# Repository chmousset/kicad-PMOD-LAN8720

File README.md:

# PMOD-LAN8720

This is a single-width PMOD module with the RMII 10/100BASE-T PHY LAN8720. Contrary to most similar Ethernet PHY extensions, this one requires the refclk signal has to be provided from the host. It can be useful when multiple PHY have to be connected as it can reduce usage of clock-domain crossing.

## Configuration
The configuration straps are set for RMII slave operation, and link autonegociation. The MDIO is broken down on an extra connector for diagnostic or testing purposes. PHY ID 0 is used.

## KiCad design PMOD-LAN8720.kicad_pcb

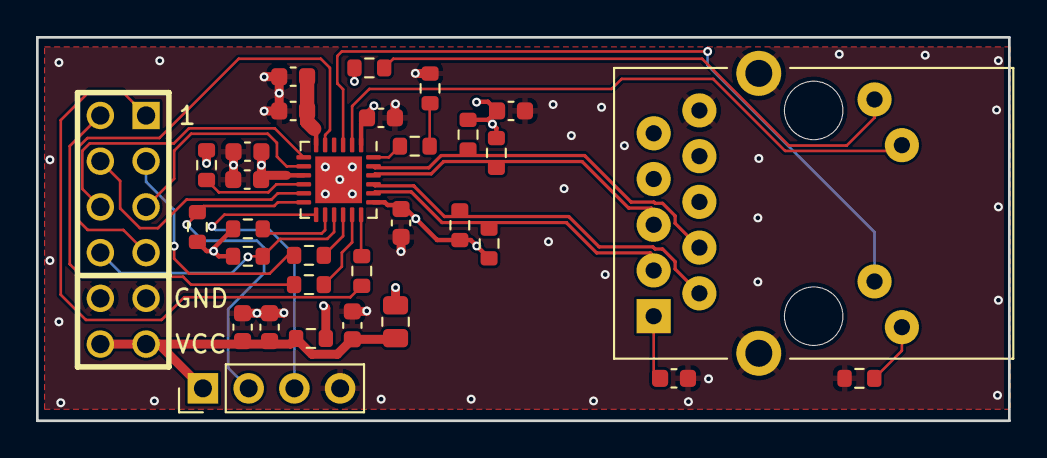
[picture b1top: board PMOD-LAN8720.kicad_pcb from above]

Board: 4 copper layers, 54.0 x 21.3 mm, 32 parts (0 on the bottom side), 31 nets.

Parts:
C10, C17, C22: 4.7u; C_0603_1608Metric
C12, C14, C23, C24, C27: 100n; C_0603_1608Metric
C15: 10p; C_0603_1608Metric
C19: 470p; C_0603_1608Metric
C21: 20p; C_0603_1608Metric
FB2: 100@100M; R_0805_2012Metric
J1: Conn_01x03; PinHeader_1x04_P2.54mm_Vertical
J2: RB1-125B8G1A; RJ45_UDE_RB1-125B8G1A
PMOD1: PMOD-Device-x2-Type-1A-GPIO; pmod_pin_array_6x2
R20, R21, R23: 2.4k; R_0603_1608Metric
R22, R38, R45, R47: 1k; R_0603_1608Metric
R25, R26, R27: 10; R_0603_1608Metric
R29: 0; R_0603_1608Metric
R31, R32, R33, R36: 49.9; R_0603_1608Metric
R37: 12k; R_0603_1608Metric
U5: LAN8720A; QFN-24-1EP_4x4mm_P0.5mm_EP2.6x2.6mm

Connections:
+3.3V: C10.2, C12.2, C22.2, FB2.1, J1.1, PMOD1.6 (VCC), PMOD1.12 (VCC), R29.1
/LED1_T: J2.L3, U5.3 (LED1/REGOFF)
/LED2_T: J2.L2, U5.2 (LED2/nINTSEL)
/MDC: J1.3, U5.13 (MDC)
/MDIO: J1.2, R22.1, U5.12 (MDIO)
/REFCLK: PMOD1.4 (IOA3), U5.5 (XTAL1/CLKIN)
/RST: PMOD1.10 (IOB3), R21.1, U5.15 (RST)
/RX_D0: PMOD1.3 (IOA2), U5.8 (RXD0/MODE0)
/RX_D1: PMOD1.9 (IOB2), U5.7 (RXD1/MODE1)
/RX_DV: PMOD1.8 (IOB1), U5.11 (CRS_DV/MODE2)
/RX_N: J2.R5 (TD2-), R36.1, U5.22 (RXN)
/RX_P: J2.R4 (TD2+), R33.1, U5.23 (RXP)
/TXEN: PMOD1.2 (IOA1), R27.2
/TX_D0: PMOD1.7 (IOB0), R25.2
/TX_D1: PMOD1.1 (IOA0), R26.2
/TX_N: J2.R3 (TD1-), R32.1, U5.20 (TXN)
/TX_P: J2.R2 (TD1+), R31.1, U5.21 (TXP)
/VDDA_T: C23.2, C24.2, C27.2, FB2.2, R31.2, R32.2, R33.2, R36.2, U5.1 (VDD2A), U5.19 (VDD1A)
/VDDCR: C17.2, C19.2, U5.6 (VDDCR)
/VDDIO_T: C14.2, C15.2, R20.2, R21.2, R22.2, R23.2, R29.2, R45.2, U5.9 (VDDIO)
GND: C10.1, C12.1, C14.1, C15.1, C17.1, C19.1, C21.1, C22.1, C23.1, C24.1, C27.1, J1.4, J2.R10 (GND), J2.SH, PMOD1.5 (GND), PMOD1.11 (GND), R38.1, R47.2, U5.25 (VSS)
unnamed: C21.2, J2.R1 (CT)
unnamed: J2.L1, R45.1
unnamed: J2.L4, R47.1
unnamed: R37.1, R38.2
unnamed: R20.1, U5.14 (INT/REFCLKO)
unnamed: R37.2, U5.24 (RBIAS)
unnamed: R23.1, U5.10 (RXER/PHYAD0)
unnamed: R25.1, U5.17 (TXD0)
unnamed: R26.1, U5.18 (TXD1)
unnamed: R27.1, U5.16 (TXEN)

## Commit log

2024-04-17 [init] created repo
